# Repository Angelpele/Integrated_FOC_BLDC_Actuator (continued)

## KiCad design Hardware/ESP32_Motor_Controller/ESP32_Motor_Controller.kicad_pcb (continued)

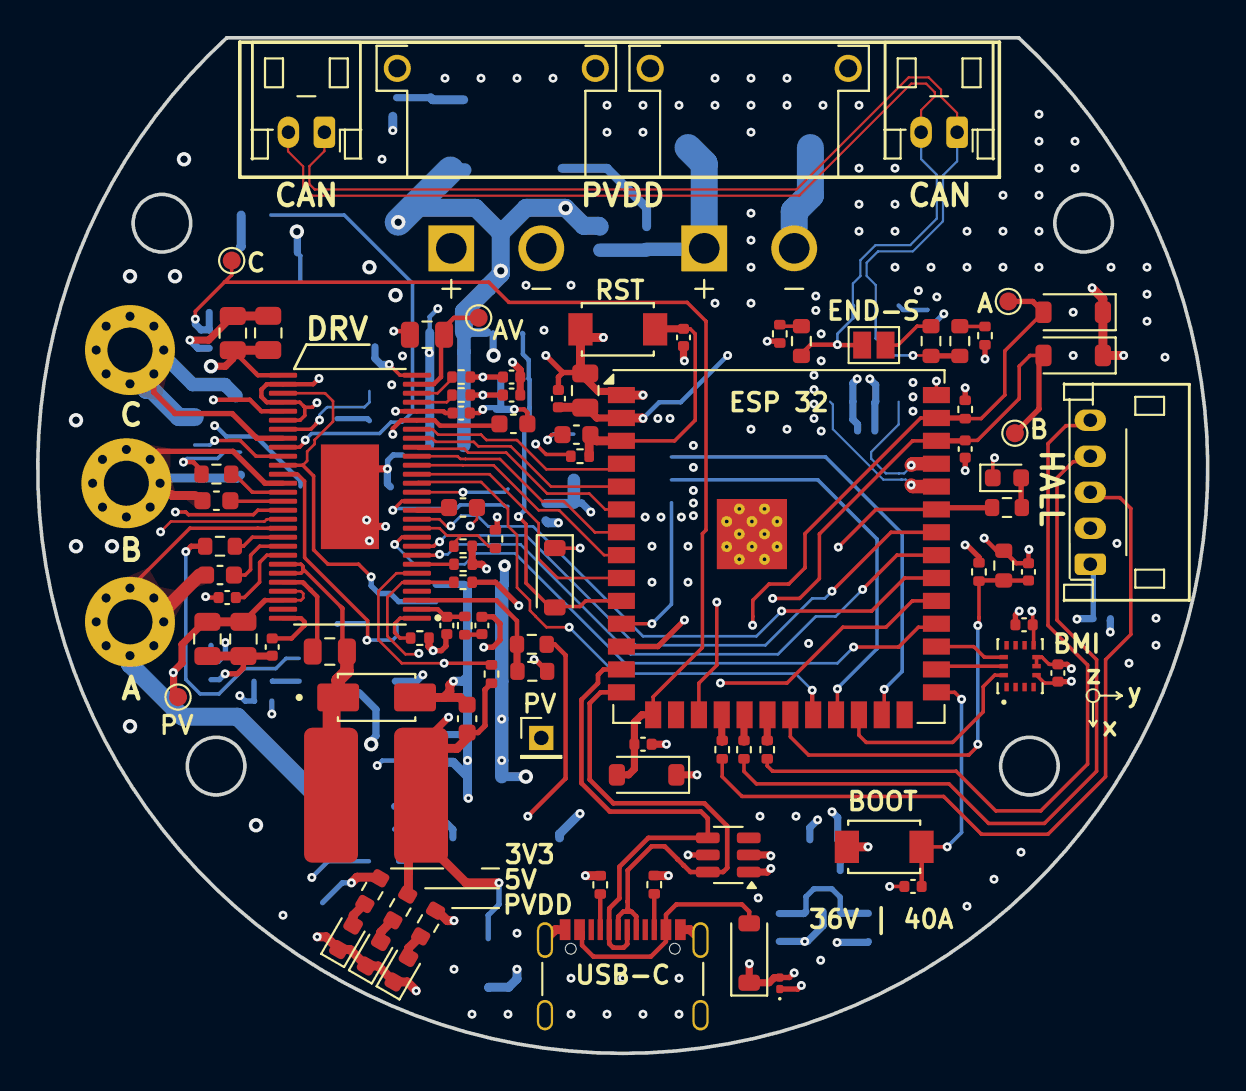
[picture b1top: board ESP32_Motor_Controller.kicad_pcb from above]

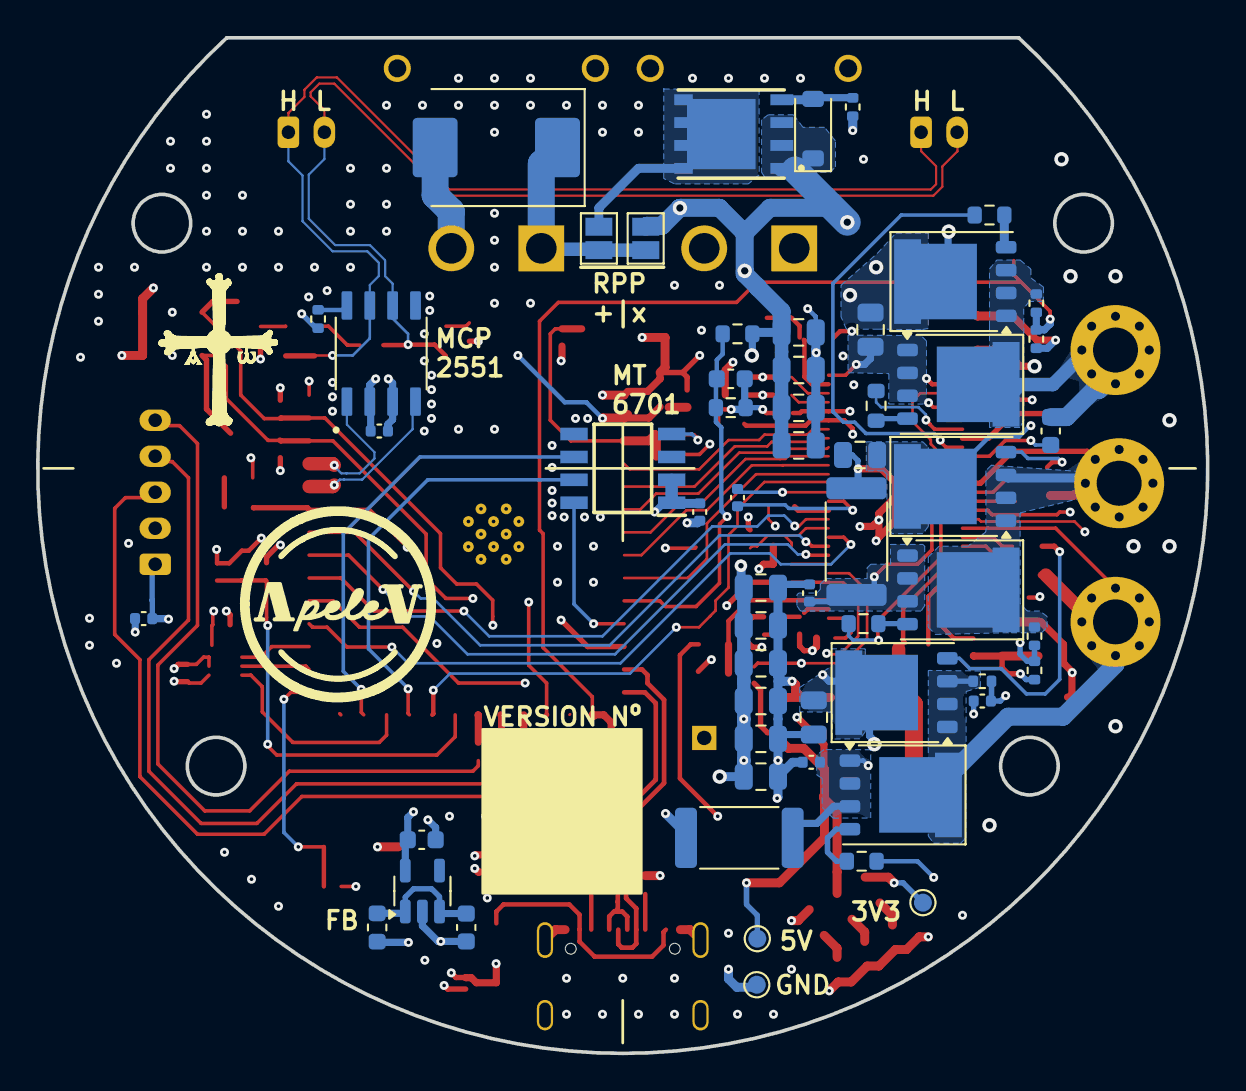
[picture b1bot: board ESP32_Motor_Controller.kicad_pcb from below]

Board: 4 copper layers, 65.0 x 56.4 mm, 154 parts (60 on the bottom side), 96 nets.

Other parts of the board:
A: A_SENSE; TestPoint_Pad_D1.0mm
AV: AVDD; TestPoint_Pad_D1.0mm
B: B_SENSE; TestPoint_Pad_D1.0mm
C: C_SENSE; TestPoint_Pad_D1.0mm
ESP 32: ESP32-S3-WROOM-1; ESP32-S3-WROOM-1U
FB: -k; L_0603_1608Metric
GND: GND; TestPoint_Pad_D1.0mm
PV: PVDD; TestPoint_Pad_D1.0mm
USB-C: USB_C 3.1; USB_C_Receptacle_Palconn_UTC16-G

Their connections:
3V3: ESP 32.2 (3V3); also elsewhere on the board
5V: FB.1; also elsewhere on the board
/CONTROLLER/BOOT: ESP 32.27 (GPIO0/BOOT); also elsewhere on the board
/CONTROLLER/EN: ESP 32.3 (EN); also elsewhere on the board
/GATE DRIVER/AVDD: AV.1; also elsewhere on the board
AGND: ESP 32.1 (GND), ESP 32.40 (GND), ESP 32.41 (GND), GND.1, USB-C.A1 (GND), USB-C.A12 (GND), USB-C.B1 (GND), USB-C.B12 (GND), USB-C.S1 (SHIELD); also elsewhere on the board
A_SENSE: A.1, ESP 32.39 (GPIO1/TOUCH1/ADC1_CH0); also elsewhere on the board
BMI_CS: ESP 32.29 (SPIIO7/GPIO36/FSPICLK/SUBSPICLK); also elsewhere on the board
BMI_SCK: ESP 32.28 (SPIIO6/GPIO35/FSPID/SUBSPID); also elsewhere on the board
BMI_SDA: ESP 32.24 (GPIO47/SPICLK_P/SUBSPICLK_P_DIFF); also elsewhere on the board
B_SENSE: B.1, ESP 32.38 (GPIO2/TOUCH2/ADC1_CH1); also elsewhere on the board
CAN_RX: ESP 32.36 (U0RXD/GPIO44/CLK_OUT2); also elsewhere on the board
CAN_TX: ESP 32.37 (U0TXD/GPIO43/CLK_OUT1); also elsewhere on the board
C_SENSE: C.1, ESP 32.15 (GPIO3/TOUCH3/ADC1_CH2); also elsewhere on the board
DC_CAL: ESP 32.32 (MTCK/GPIO39/CLK_OUT3/SUBSPICS1); also elsewhere on the board
EN_GATE: ESP 32.22 (GPIO14/TOUCH14/ADC2_CH3/FSPIWP/FSPIDQS/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); also elsewhere on the board
GAIN: ESP 32.30 (SPIDQS/GPIO37/FSPIQ/SUBSPIQ); also elsewhere on the board
HALL_A: ESP 32.18 (GPIO10/TOUCH10/ADC1_CH9/FSPICS0/FSPIIO4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); also elsewhere on the board
HALL_B: ESP 32.19 (GPIO11/TOUCH11/ADC2_CH0/FSPID/FSPIIO5/S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); also elsewhere on the board
HALL_C: ESP 32.20 (GPIO12/TOUCH12/ADC2_CH1/FSPICLK/FSPIIO6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); also elsewhere on the board
INH_A: ESP 32.9 (GPIO16/U0CTS/ADC2_CH5/XTAL_32K_N); also elsewhere on the board
INH_B: ESP 32.7 (GPIO7/TOUCH7/ADC1_CH6); also elsewhere on the board
INH_C: ESP 32.5 (GPIO5/TOUCH5/ADC1_CH4); also elsewhere on the board
INL_A: ESP 32.8 (GPIO15/U0RTS/ADC2_CH4/XTAL_32K_P); also elsewhere on the board
INL_B: ESP 32.6 (GPIO6/TOUCH6/ADC1_CH5); also elsewhere on the board
INL_C: ESP 32.4 (GPIO4/TOUCH4/ADC1_CH3); also elsewhere on the board
MAG_CLK: ESP 32.23 (GPIO21); also elsewhere on the board
MAG_CSN: ESP 32.11 (GPIO18/U1RXD/ADC2_CH7/CLK_OUT3); also elsewhere on the board
MAG_DO: ESP 32.25 (GPIO48/SPICLK_N/SUBSPICLK_N_DIFF); also elsewhere on the board
M_OC: ESP 32.34 (MTDI/GPIO41/CLK_OUT1); also elsewhere on the board
M_PWM: ESP 32.33 (MTDO/GPIO40/CLK_OUT2); also elsewhere on the board
NFAULT: ESP 32.35 (MTMS/GPIO42); also elsewhere on the board
NOCTW: ESP 32.31 (GPIO38/FSPIWP/SUBSPIWP); also elsewhere on the board
NTC: ESP 32.21 (GPIO13/TOUCH13/ADC2_CH2/FSPIQ/FSPIIO7/S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); also elsewhere on the board
unnamed 50: USB-C.A4 (VBUS), USB-C.A9 (VBUS), USB-C.B4 (VBUS), USB-C.B9 (VBUS); also elsewhere on the board
unnamed 66: FB.2; also elsewhere on the board
unnamed 83: USB-C.A5 (CC1); also elsewhere on the board
unnamed 84: USB-C.B5 (CC2); also elsewhere on the board
PVDD: PV.1; also elsewhere on the board
PVDD_SENSE: ESP 32.10 (GPIO17/U1TXD/ADC2_CH6); also elsewhere on the board
SO1: ESP 32.12 (GPIO8/TOUCH8/ADC1_CH7/SUBSPICS1); also elsewhere on the board
SO2: ESP 32.17 (GPIO9/TOUCH9/ADC1_CH8/FSPIHD/SUBSPIHD); also elsewhere on the board
USB_DN: ESP 32.13 (GPIO19/U1RTS/ADC2_CH8/CLK_OUT2/USB_D-), USB-C.A7 (D-), USB-C.B7 (D-); also elsewhere on the board
USB_DP: ESP 32.14 (GPIO20/U1CTS/ADC2_CH9/CLK_OUT1/USB_D+), USB-C.A6 (D+), USB-C.B6 (D+); also elsewhere on the board

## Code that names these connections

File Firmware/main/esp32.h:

// GENERAL GPIO //

#define USB_DP 20
#define USB_DN 19

#define BOOT 0

#define CAN_RX 44
#define CAN_TX 43

#define PVDD_SENSE 17

// DRV8302 GPIO //
#define A_SENSE 1
#define B_SENSE 2
#define C_SENSE 3

#define INL_A 15
#define INH_A 16
#define INL_B 6
#define INH_B 7
#define INL_C 4
#define INH_C 5

#define DC_CAL 39
#define MPWM 40
#define MOC 41
#define NFAULT 42
#define NOCTW 38

#define GAIN 37
#define SO1 8
#define SO2 9

#define EN_DRV 14

// SENSORS //

#define HALL_A 10
#define HALL_B 11
#define HALL_C 12

#define BMI_SDA 47  // 3 Wire SPI
#define BMI_SCK 35
#define BMI_CS 36

#define MAG_DO ((gpio_num_t)48)   // 3 Wire SPI - One way (SSI)
#define MAG_CSN ((gpio_num_t)18)
#define MAG_CLK ((gpio_num_t)21)

#define NTC 13

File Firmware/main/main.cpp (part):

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            case SYSTEM_INIT:
            {       
                
                gpio_set_pull_mode(CAN_RX, GPIO_PULLUP_ONLY); // GPIO44
                gpio_set_pull_mode(CAN_TX, GPIO_PULLUP_ONLY); // GPIO43

                if (initialize() == 0) {
                    system_state = SYSTEM_CALIBRATION;
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
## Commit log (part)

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2025-11-03 Finished Schematics
2025-11-03 README Update
2025-11-13 PCB Layout Update
2025-11-17 Update Layout
2025-11-22 Finished Layout V1
2025-12-18 Update
    Mag_first_sketch
2026-02-04 Update code
2026-02-06 Fusion download
2026-02-07 Media Upddate
2026-02-23 Test firmware
2026-03-08 PCB V2, CAD V3 & Code
2026-03-20 Definitive CAD
2026-04-02 Code update
    Motor moving
2026-04-03 Updated Code - Fast spin, No shake
    Closed loop with magnet
2026-04-14 PCB_V2
2026-04-15 Revise README for FOC Controller project
    Updated project description and features for clarity and detail. Enhanced hardware and software sections with specific components and functionalities.
2026-04-15 Adjust image heights in README
    Reduced image heights in the README for better layout.
2026-04-15 Update README with improved SPWM stage details
    Clarified description of the Closed Loop SPWM stage in the README.
2026-04-15 Remove Qihao Guo reference from README
    Removed a reference to Qihao Guo's YouTube channel.
2026-05-02 Finished BMI
2026-05-03 Included more control modes and parameter change from monitor
2026-05-03 Tunning ramp and spinning parameters
    Spin parameters improved, ramp in progress
2026-05-05 Buck Components Update
2026-05-08 CAN_Bus
    MCP2551 is transmitting packets
2026-05-09 Slave_Master_CAN
2026-05-11 FOC Loop Implementation
2026-05-12 Update FOC PID tunning
2026-06-03 FOC + Vel + Pos Loop (Shake)
2026-06-21 Reducer PID Controller Calibrated
